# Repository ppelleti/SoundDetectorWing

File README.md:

This repository contains [KiCad][1] 5 files for a [FeatherWing][2]
board which lets you plug in a [SparkFun Sound Detector][3] and use it
with a Feather.  It runs the Sound Detector at 5V, and then has
voltage dividers to convert the output signals to 3.3V, for use by the
Feather.

The "audio" analog signal is connected to feather pin A0, the
"envelope" analog signal is connected to feather pin A1, and the
"gate" digital signal is connected to the feather pin that
[I call F0][4].  There is also a potentiometer connected to feather
pin A2, which can be used, for example, if you want to implement an
adjustable threshold in software (rather than using the Sound
Detector's "gate" signal).

The board has three M2.5 mounting holes which should line up with the
Feather, and two M3 mounting holes which should line up with the Sound
Detector. There are optional places for two SMT decoupling capacitors.

SparkFun recommends running the Sound Detector at 5V, rather than
3.3V, so the Sound Detector is powered from the Feather's VUSB pin, to
get a solid 5V supply.  A consequence of this is that *this
FeatherWing will not work on battery power*; you must have USB plugged
in for power.

* [View schematic](SoundDetectorWing.pdf)
* [Order board on OSH Park][5] (photo shows the OSH Park "after dark" option)

## Bill of Materials

| Ref        | Description                      | MPN              | Digi-Key PN              |
| ---------- | -------------------------------- | ---------------- | ------------------------ |
| C1, C2     | CAP CER 10UF 10V X5R 0805        | C0805C106K8PACTU | [399-4925-1-ND][C1]      |
| J1         | 16-pin male header 2.54mm        |                  |                          |
| J2         | 12-pin male header 2.54mm        |                  |                          |
| J3         | CONN HDR 5POS 0.1 GOLD PCB       | PPPC051LFBN-RC   | [S7038-ND][J3]           |
| R1, R3, R5 | RES 1.74K OHM 1/4W 1% AXIAL      | MFR-25FBF52-1K74 | [1.74KXBK-ND][R1]        |
| R2, R4, R6 | RES 3.3K OHM 1/4W 1% AXIAL       | RNMF14FTC3K30    | [S3.3KCACT-ND][R2]       |
| RV1        | POT 10K OHM THUMBWHEEL CERM ST   | 3352T-1-103LF    | [3352T-103LF-ND][RV1]    |

[C1]: https://www.digikey.com/products/en?keywords=399-4925-1-ND
[J3]: https://www.digikey.com/products/en?keywords=S7038-ND
[R1]: https://www.digikey.com/products/en?keywords=1.74KXBK-ND
[R2]: https://www.digikey.com/products/en?keywords=S3.3KCACT-ND
[RV1]: https://www.digikey.com/products/en?keywords=3352T-103LF-ND

[1]: http://kicad.org/
[2]: https://learn.adafruit.com/adafruit-feather/feather-specification
[3]: https://www.sparkfun.com/products/12642
[4]: https://funwithsoftware.org/posts/2018-08-31-feather-ascii-art-pinout.html
[5]: https://oshpark.com/shared_projects/fDlbdMGa

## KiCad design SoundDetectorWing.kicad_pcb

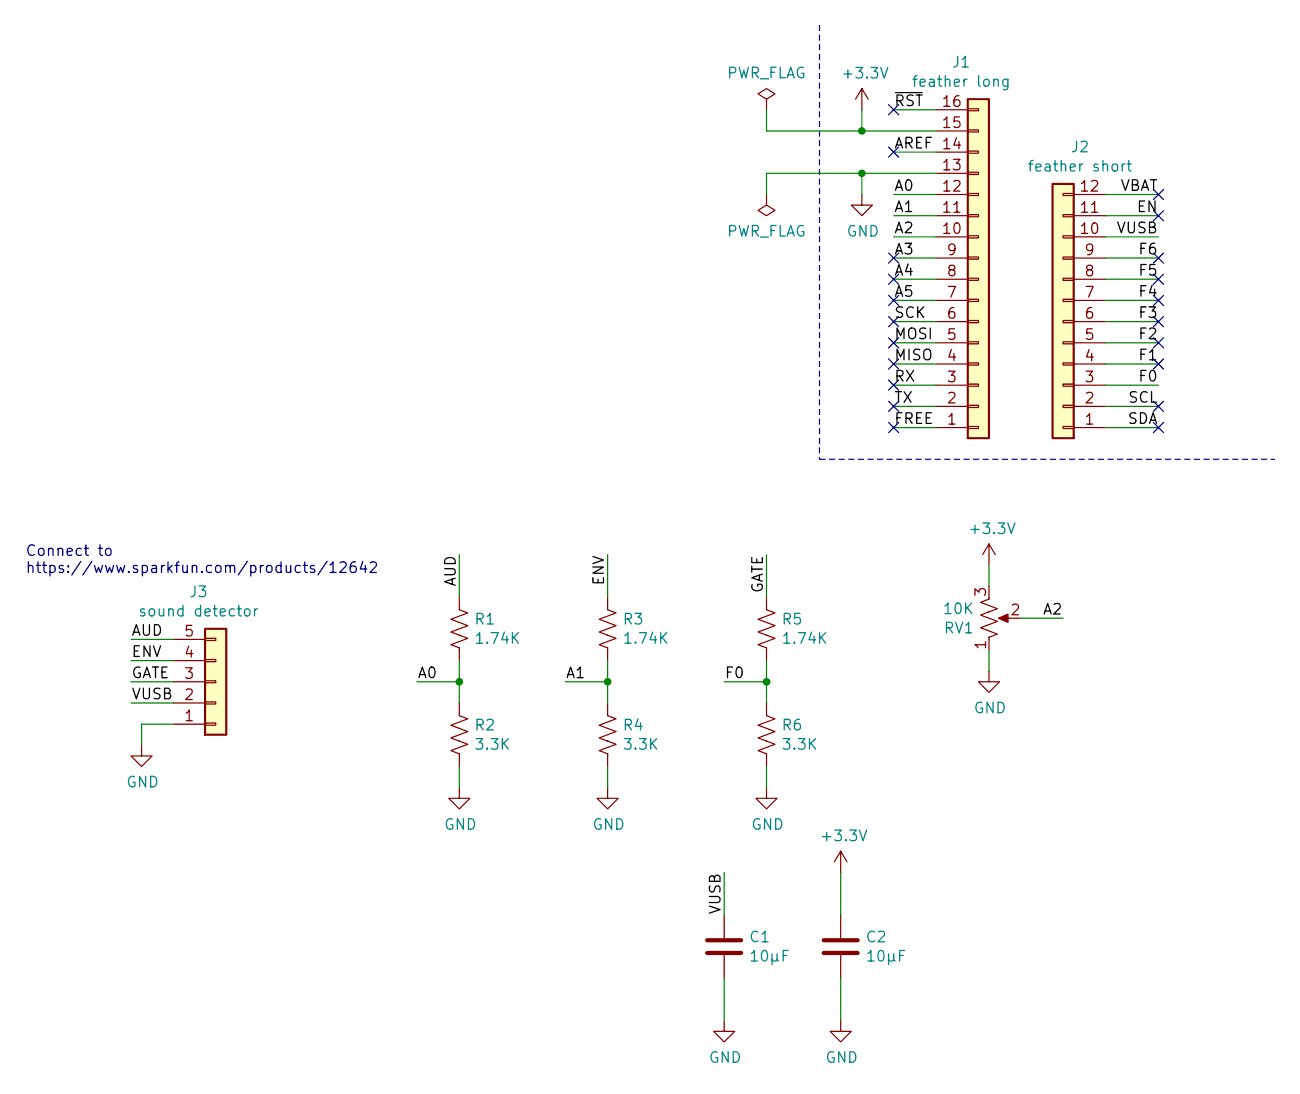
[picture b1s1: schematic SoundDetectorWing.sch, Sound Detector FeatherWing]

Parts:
C1, C2: 10μF; C_0805_2012Metric_Pad1.15x1.40mm_HandSolder; MPN C0805C106K8PACTU; Digi-Key_PN 399-4925-1-ND
J1: feather long; PinHeader_1x16_P2.54mm_Vertical
J2: feather short; PinHeader_1x12_P2.54mm_Vertical
J3: sound detector; PinSocket_1x05_P2.54mm_Vertical; MPN PPPC051LFBN-RC; Digi-Key_PN S7038-ND
R1, R3, R5: 1.74K; R_Axial_DIN0207_L6.3mm_D2.5mm_P7.62mm_Horizontal; MPN MFR-25FBF52-1K74; Digi-Key_PN 1.74KXBK-ND
R2, R4, R6: 3.3K; R_Axial_DIN0207_L6.3mm_D2.5mm_P7.62mm_Horizontal; MPN RNMF14FTC3K30; Digi-Key_PN S3.3KCACT-ND
RV1: 10K; Potentiometer_Bourns_3352T_Vertical; MPN 3352T-1-103LF; Digi-Key_PN 3352T-103LF-ND

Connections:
+3V3: C2.1, J1.15, RV1.3
/A0: J1.12, R1.2, R2.1
/A1: J1.11, R3.2, R4.1
/A2: J1.10, RV1.2
/A3: J1.9
/A4: J1.8
/A5: J1.7
/AREF: J1.14
/AUD: J3.5, R1.1
/EN: J2.11
/ENV: J3.4, R3.1
/F0: J2.3, R5.2, R6.1
/F1: J2.4
/F2: J2.5
/F3: J2.6
/F4: J2.7
/F5: J2.8
/F6: J2.9
/FREE: J1.1
/GATE: J3.3, R5.1
/MISO: J1.4
/MOSI: J1.5
/RX: J1.3
/SCK: J1.6
/SCL: J2.2
/SDA: J2.1
/TX: J1.2
/VBAT: J2.12
/VUSB: C1.1, J2.10, J3.2
/~RST: J1.16
GND: C1.2, C2.2, J1.13, J3.1, R2.2, R4.2, R6.2, RV1.1

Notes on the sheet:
Connect to https://www.sparkfun.com/products/12642

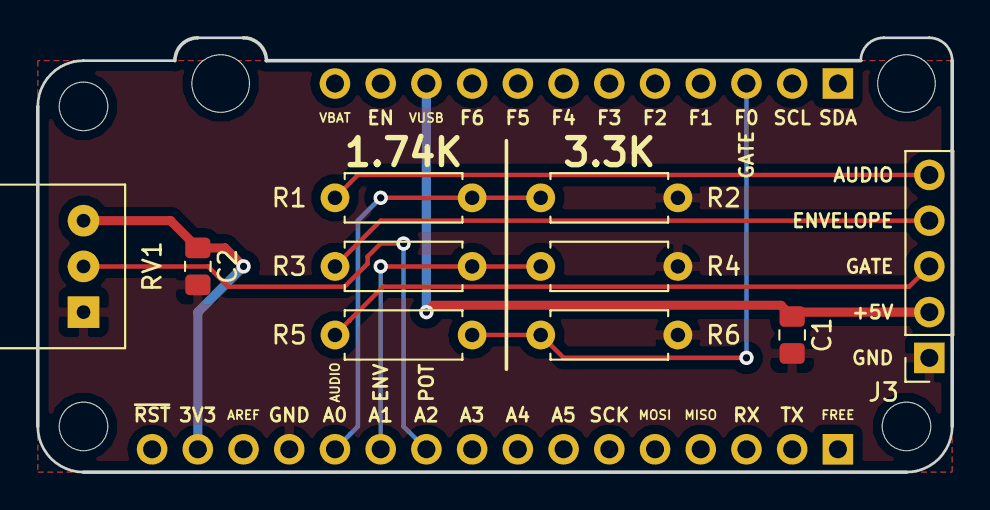
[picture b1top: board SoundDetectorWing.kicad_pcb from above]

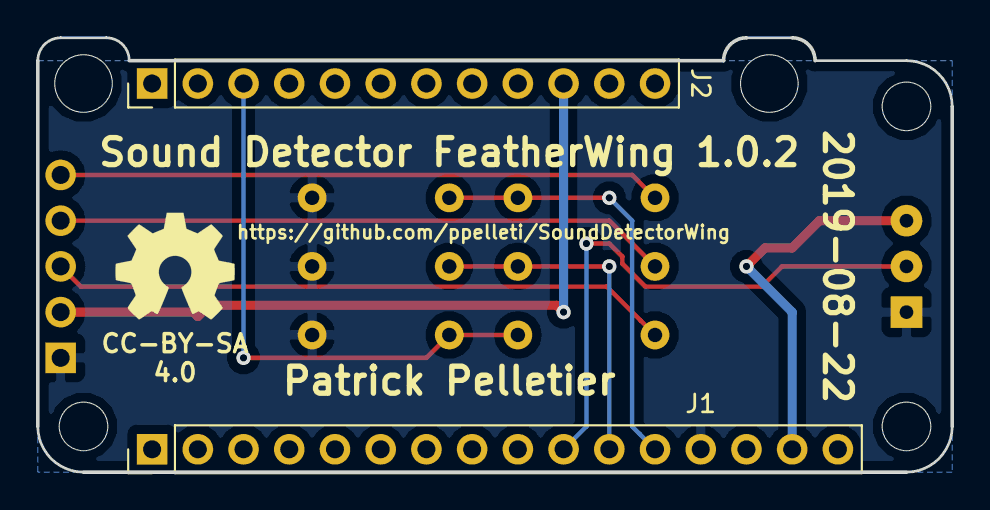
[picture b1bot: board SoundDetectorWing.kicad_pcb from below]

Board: 2 copper layers, 50.8 x 24.1 mm, 12 parts (2 on the bottom side), 10 nets.

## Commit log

2019-07-24 Initial commit.
2019-07-24 Draw schematic.
2019-07-24 Use VUSB instead of +5V.
2019-07-24 Got it passing ERC.
2019-07-24 Add a couple decouplng capacitors, in case they are needed.
2019-07-24 Assign footprints.
2019-07-24 Add thumbwheel potentiometer footprint.
2019-07-24 Assign potentiometer footprint.
2019-07-24 Import new footprints into PCB.
2019-07-24 Position footprints on PCB.
2019-07-24 Draw all the tracks.
2019-07-24 Fill GND zones.
2019-07-24 Netlist.
2019-07-24 Add information on back silkscreen.
2019-07-24 Add metadata to schematic.
2019-07-24 Put GitHub URL on silkscreen.
2019-08-03 Add PDF of schematic.
2019-08-09 Rename files to SoundDetectorWing.
2019-08-09 Add screw holes to line up with SparkFun Sound Detector board.
2019-08-09 Label the functions of the feather pins.
2019-08-22 Finally get SoundDetector mounting holes in correct place.
2019-08-22 Adjust board outline.
2019-08-22 Update version number.
2019-09-09 Add BOM.
2019-09-09 Use male header.
2019-10-02 Add license, README, and photo.
2019-10-02 Use smaller photo.
2019-10-02 Link to board on OSH Park.
2019-10-02 Mention that USB power is required.
2019-10-02 Ugh, "y" in battery.
2021-10-22 Link to kicad.org
    https://forum.kicad.info/t/warning-avoid-all-links-to-kicad-pcb-org-use-kicad-org/31521

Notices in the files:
SoundDetectorWing.kicad_pcb:
CC-BY-SA
